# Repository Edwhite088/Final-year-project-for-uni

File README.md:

# Final-year-project-for-uni

This is my final year project for university
This is still a work in progress so subject to change

My project is a mobile tank like robot with a gyroscopic stabilisation system on top to act as a tray
This project uses 2 arduino unos 1 sn754410ne H-brigdes, 2 l298n motor controller boards, 4 linear motors and 2 12v brushed motors

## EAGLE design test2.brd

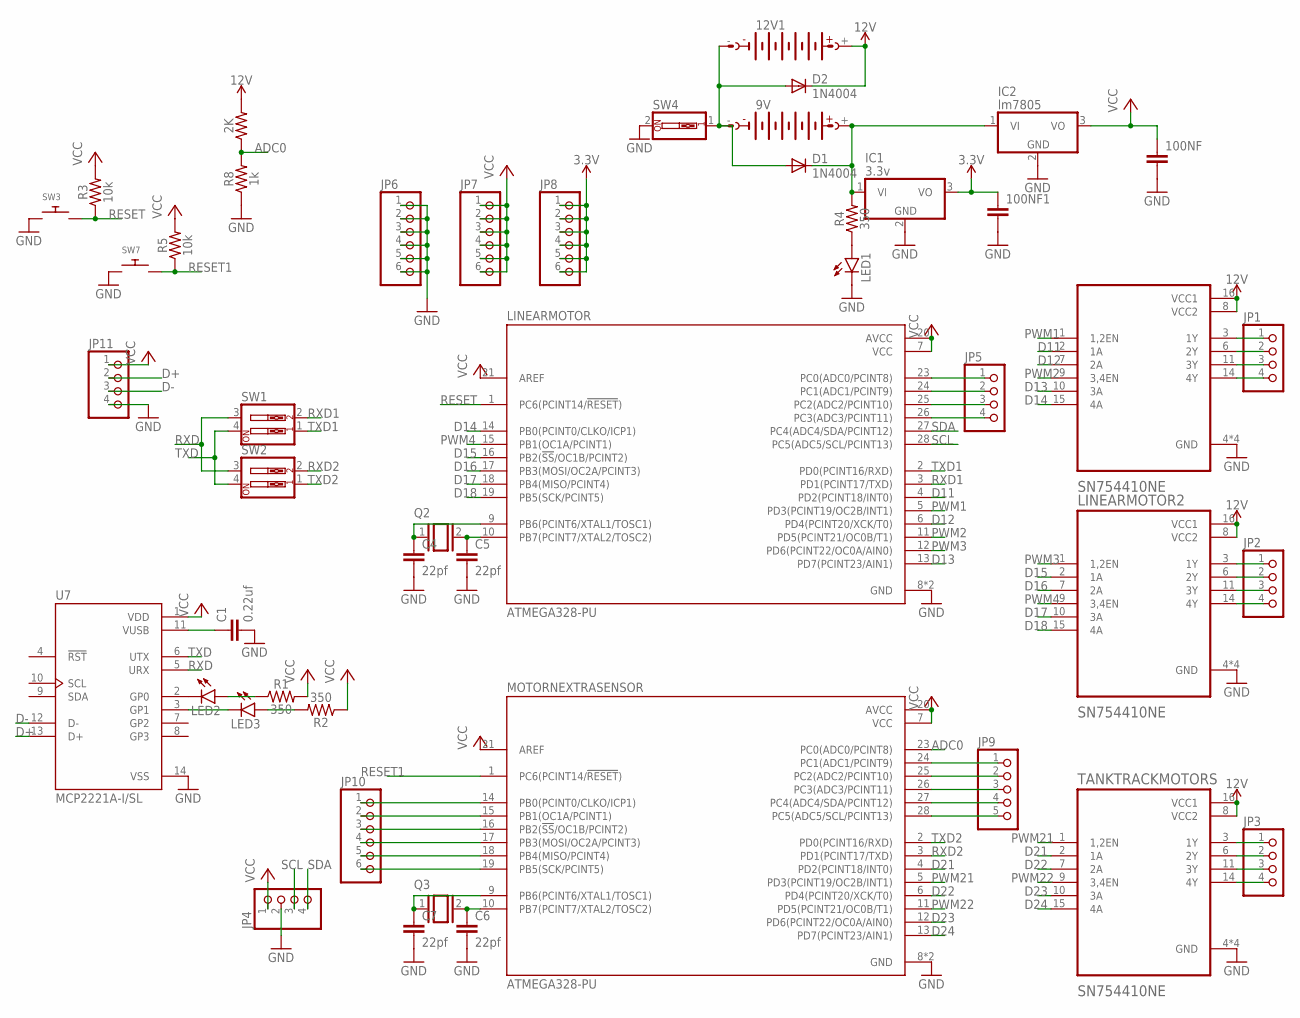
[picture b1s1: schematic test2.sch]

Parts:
2K: 2k; AXIAL-0.3
9V, 12V1: AB9V
100NF, 100NF1: 330nF; CAP-PTH-10MM
C1: 0.22uf; CAP-PTH-10MM
C4, C5, C6, C7: 22pf; CAP-PTH-10MM
D1, D2: 1N4004; DO41-10
IC1: 3.3v; TO220V
IC2: lm7805; TO220V
JP1, JP2, JP3, JP4, JP5, JP11: PINHD-1X4; 1X04
JP6, JP7, JP8, JP10: PINHD-1X6; 1X06
JP9: PINHD-1X5; 1X05
LED1, LED2, LED3: LED3MM
LINEARMOTOR: ATMEGA328-PU; DIP787W46P254L3467H508Q28
LINEARMOTOR1, LINEARMOTOR2: SN754410NE; DIP762W45P254L1980H508Q16
MOTORNEXTRASENSOR: ATMEGA328-PU; DIP787W46P254L3467H508Q28
Q2, Q3: XTAL/S; QS
R1, R2, R4: 350; AXIAL-0.3
R3, R5: 10k; AXIAL-0.3
R8: 1k; AXIAL-0.3
SW1, SW2: SW_DIP-2; EDG-02
SW3, SW7: SWITCH_PUSHBUTTONEVQ-PE; TACT_PANA-EVQ
SW4: SW_DIP-1; EDG-01
TANKTRACKMOTORS: SN754410NE; DIP762W45P254L1980H508Q16
U7: MCP2221A-I/SL; SOIC127P600X175-14N

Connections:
3.3V: 100NF1.1, IC1.3 (VO), JP8.1, JP8.2, JP8.3, JP8.4, JP8.5, JP8.6
12V: 2K.P$2 (2), 12V1.+, D2.C, LINEARMOTOR1.8 (VCC2), LINEARMOTOR1.16 (VCC1), LINEARMOTOR2.8 (VCC2), LINEARMOTOR2.16 (VCC1), TANKTRACKMOTORS.8 (VCC2), TANKTRACKMOTORS.16 (VCC1)
ADC0: 2K.P$1 (1), MOTORNEXTRASENSOR.23 (PC0(ADC0/PCINT8)), R8.P$2 (2)
D11: LINEARMOTOR.4 (PD2(PCINT18/INT0)), LINEARMOTOR1.2 (1A)
D12: LINEARMOTOR.6 (PD4(PCINT20/XCK/T0)), LINEARMOTOR1.7 (2A)
D13: LINEARMOTOR.13 (PD7(PCINT23/AIN1)), LINEARMOTOR1.10 (3A)
D14: LINEARMOTOR.14 (PB0(PCINT0/CLKO/ICP1)), LINEARMOTOR1.15 (4A)
D15: LINEARMOTOR.16 (PB2(!SS!/OC1B/PCINT2)), LINEARMOTOR2.2 (1A)
D16: LINEARMOTOR.17 (PB3(MOSI/OC2A/PCINT3)), LINEARMOTOR2.7 (2A)
D17: LINEARMOTOR.18 (PB4(MISO/PCINT4)), LINEARMOTOR2.10 (3A)
D18: LINEARMOTOR.19 (PB5(SCK/PCINT5)), LINEARMOTOR2.15 (4A)
D21: MOTORNEXTRASENSOR.4 (PD2(PCINT18/INT0)), TANKTRACKMOTORS.2 (1A)
D22: MOTORNEXTRASENSOR.6 (PD4(PCINT20/XCK/T0)), TANKTRACKMOTORS.7 (2A)
D23: MOTORNEXTRASENSOR.12 (PD6(PCINT22/OC0A/AIN0)), TANKTRACKMOTORS.10 (3A)
D24: MOTORNEXTRASENSOR.13 (PD7(PCINT23/AIN1)), TANKTRACKMOTORS.15 (4A)
D+: JP11.2, U7.13 (D+)
D-: JP11.3, U7.12 (D-)
GND: 100NF.2, 100NF1.2, C1.2, C4.2, C5.2, C6.2, C7.2, IC1.2 (GND), IC2.2 (GND), JP4.2, JP6.1, JP6.2, JP6.3, JP6.4, JP6.5, JP6.6, JP11.4, LED1.K (C), LINEARMOTOR.8 (GND), LINEARMOTOR.22 (GND), LINEARMOTOR1.4 (GND), LINEARMOTOR1.5 (GND), LINEARMOTOR1.12 (GND), LINEARMOTOR1.13 (GND), LINEARMOTOR2.4 (GND), LINEARMOTOR2.5 (GND), LINEARMOTOR2.12 (GND), LINEARMOTOR2.13 (GND), MOTORNEXTRASENSOR.8 (GND), MOTORNEXTRASENSOR.22 (GND), R8.P$1 (1), SW3.P$1, SW4.2, SW7.P$1, TANKTRACKMOTORS.4 (GND), TANKTRACKMOTORS.5 (GND), TANKTRACKMOTORS.12 (GND), TANKTRACKMOTORS.13 (GND), U7.14 (VSS)
unnamed: C1.1, U7.11 (VUSB)
unnamed: LED2.K (C), U7.2 (GP0)
unnamed: LED3.K (C), U7.3 (GP1)
unnamed: LED2.A, R1.P$1 (1)
unnamed: LED3.A, R2.P$2 (2)
unnamed: C6.1, MOTORNEXTRASENSOR.10 (PB7(PCINT7/XTAL2/TOSC2)), Q3.2
unnamed: C7.1, MOTORNEXTRASENSOR.9 (PB6(PCINT6/XTAL1/TOSC1)), Q3.1
unnamed: C4.1, LINEARMOTOR.9 (PB6(PCINT6/XTAL1/TOSC1)), Q2.1
unnamed: JP9.1, MOTORNEXTRASENSOR.24 (PC1(ADC1/PCINT9))
unnamed: C5.1, LINEARMOTOR.10 (PB7(PCINT7/XTAL2/TOSC2)), Q2.2
unnamed: JP1.1, LINEARMOTOR1.3 (1Y)
unnamed: JP1.2, LINEARMOTOR1.6 (2Y)
unnamed: JP1.3, LINEARMOTOR1.11 (3Y)
unnamed: JP1.4, LINEARMOTOR1.14 (4Y)
unnamed: JP2.1, LINEARMOTOR2.3 (1Y)
unnamed: JP2.2, LINEARMOTOR2.6 (2Y)
unnamed: JP2.3, LINEARMOTOR2.11 (3Y)
unnamed: JP2.4, LINEARMOTOR2.14 (4Y)
unnamed: JP3.1, TANKTRACKMOTORS.3 (1Y)
unnamed: JP3.2, TANKTRACKMOTORS.6 (2Y)
unnamed: JP3.3, TANKTRACKMOTORS.11 (3Y)
unnamed: JP3.4, TANKTRACKMOTORS.14 (4Y)
unnamed: JP5.1, LINEARMOTOR.23 (PC0(ADC0/PCINT8))
unnamed: JP5.2, LINEARMOTOR.24 (PC1(ADC1/PCINT9))
unnamed: JP5.3, LINEARMOTOR.25 (PC2(ADC2/PCINT10))
unnamed: JP5.4, LINEARMOTOR.26 (PC3(ADC3/PCINT11))
unnamed: JP9.2, MOTORNEXTRASENSOR.25 (PC2(ADC2/PCINT10))
unnamed: JP9.3, MOTORNEXTRASENSOR.26 (PC3(ADC3/PCINT11))
unnamed: JP10.1, MOTORNEXTRASENSOR.14 (PB0(PCINT0/CLKO/ICP1))
unnamed: JP10.2, MOTORNEXTRASENSOR.15 (PB1(OC1A/PCINT1))
unnamed: JP10.3, MOTORNEXTRASENSOR.16 (PB2(!SS!/OC1B/PCINT2))
unnamed: JP10.4, MOTORNEXTRASENSOR.17 (PB3(MOSI/OC2A/PCINT3))
unnamed: JP10.5, MOTORNEXTRASENSOR.18 (PB4(MISO/PCINT4))
unnamed: JP9.4, MOTORNEXTRASENSOR.27 (PC4(ADC4/SDA/PCINT12))
unnamed: JP9.5, MOTORNEXTRASENSOR.28 (PC5(ADC5/SCL/PCINT13))
unnamed: 9V.+, D1.C, IC1.1 (VI), IC2.1 (VI), R4.P$2 (2)
unnamed: JP10.6, MOTORNEXTRASENSOR.19 (PB5(SCK/PCINT5))
unnamed: LED1.A, R4.P$1 (1)
unnamed: 9V.-, 12V1.-, D1.A, D2.A, SW4.1
PWM1: LINEARMOTOR.5 (PD3(PCINT19/OC2B/INT1)), LINEARMOTOR1.1 (1,2EN)
PWM2: LINEARMOTOR.11 (PD5(PCINT21/OC0B/T1)), LINEARMOTOR1.9 (3,4EN)
PWM3: LINEARMOTOR.12 (PD6(PCINT22/OC0A/AIN0)), LINEARMOTOR2.1 (1,2EN)
PWM4: LINEARMOTOR.15 (PB1(OC1A/PCINT1)), LINEARMOTOR2.9 (3,4EN)
PWM21: MOTORNEXTRASENSOR.5 (PD3(PCINT19/OC2B/INT1)), TANKTRACKMOTORS.1 (1,2EN)
PWM22: MOTORNEXTRASENSOR.11 (PD5(PCINT21/OC0B/T1)), TANKTRACKMOTORS.9 (3,4EN)
RESET: LINEARMOTOR.1 (PC6(PCINT14/!RESET!)), R3.P$1 (1), SW3.P$2
RESET1: MOTORNEXTRASENSOR.1 (PC6(PCINT14/!RESET!)), R5.P$1 (1), SW7.P$2
RXD: SW1.3, SW2.3, U7.5 (URX)
RXD1: LINEARMOTOR.3 (PD1(PCINT17/TXD)), SW1.2
RXD2: MOTORNEXTRASENSOR.3 (PD1(PCINT17/TXD)), SW2.2
SCL: JP4.3, LINEARMOTOR.28 (PC5(ADC5/SCL/PCINT13))
SDA: JP4.4, LINEARMOTOR.27 (PC4(ADC4/SDA/PCINT12))
TXD: SW1.4, SW2.4, U7.6 (UTX)
TXD1: LINEARMOTOR.2 (PD0(PCINT16/RXD)), SW1.1
TXD2: MOTORNEXTRASENSOR.2 (PD0(PCINT16/RXD)), SW2.1
VCC: 100NF.1, IC2.3 (VO), JP4.1, JP7.1, JP7.2, JP7.3, JP7.4, JP7.5, JP7.6, JP11.1, LINEARMOTOR.7 (VCC), LINEARMOTOR.20 (AVCC), LINEARMOTOR.21 (AREF), MOTORNEXTRASENSOR.7 (VCC), MOTORNEXTRASENSOR.20 (AVCC), MOTORNEXTRASENSOR.21 (AREF), R1.P$2 (2), R2.P$1 (1), R3.P$2 (2), R5.P$2 (2), U7.1 (VDD)

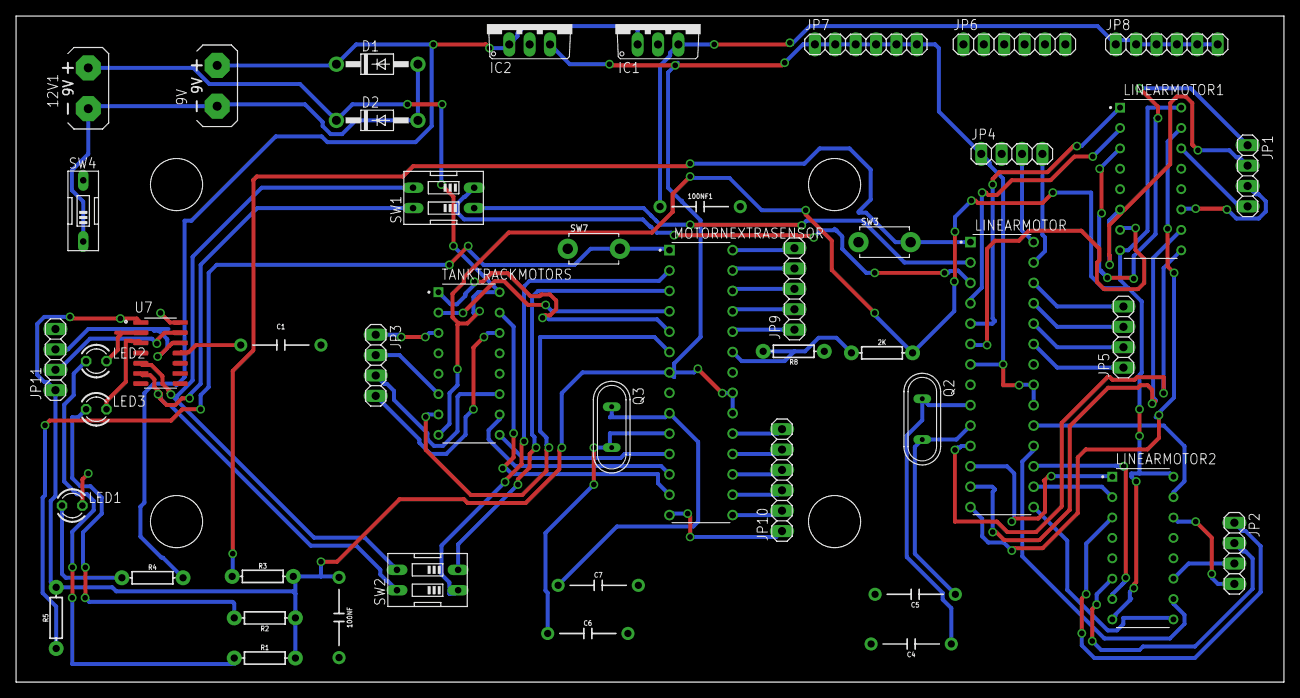
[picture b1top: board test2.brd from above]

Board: 2 copper layers, 158.0 x 83.0 mm, 47 parts (0 on the bottom side), 74 nets.

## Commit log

2024-03-25 Update PID_balance_arduino.ino
    final version that works with my project
2025-03-17 Update PID_balance_arduino.ino
    Added comments
2025-03-19 Update Year3_project_Track_movement.ino
    Added some comments

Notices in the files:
parts and their libraries:
SparkFun-Capacitors: Licensing: Creative Commons ShareAlike 4.0 International - https://creativecommons.org/licenses/by-sa/4.0
